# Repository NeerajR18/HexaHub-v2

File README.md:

# HexaHub-v2

NOTE: This is still a WIP project. Follow at your own risk!

A USB 2.0 Hub using the SL2.1A which has 4 downstream USB-A port and USB-C upstream port, with ESD and overcurrent protection enclosed in a 3D printed case with a hexagon-shaped PCB.

This USB Hub was made because of unavailability of the SL2.1S IC, which was used in the previous version and also as an improved version with polyfuses and ESD protection diodes.

This Hub was designed using KiCad and Autodesk Fusion for PCB and CAD Design. Fusion was also used for the case renders.

Made for Hack Club Fallout.

# PCB

- Schematic

- PCB without Ground Plane

- Overall PCB

# CAD

- Full Assembly

- Exploded View

# Renders
- Enclosed

- Exploded

# Build Guide
- Acquire your parts from your favourite platform.
- Order the PCB from your manufacturer
- Solder the components to the PCB
- 3D print the case, place PCB in the bottom, then close the top.
- Done!
If any footprints or 3D models are missing, you may use the footprints, symbols etc. from the Assets folder. Check your project folder and paths before importing.

# Bill of Materials

| MPN | Designator | Package | Quantity | Unit Price | Price (Ext.) | LCSC Link |
|---|---|---|---|---|---|---|
| SL2.1A | U1 | SOP-16 | 5 | 0.2677 | 1.34 | https://www.lcsc.com/product-detail/C6798314.html |
| 10.0 QHHTZB6.3 | J1 | SMD | 10 | 0.0665 | 0.67 | https://www.lcsc.com/product-detail/C668591.html |
| 676430910 | J2, J3, J4, J5 | Through Hole, Right Angle | 4 | 0.9415 | 3.77 | https://www.lcsc.com/product-detail/C2798029.html |
| 1206L200/24NR | F1 | 1206 | 5 | 0.1404 | 0.70 | https://www.lcsc.com/product-detail/C42396578.html |
| 1206L005/110WR | F2, F3, F4, F5 | 1206 | 5 | 0.1387 | 0.69 | https://www.lcsc.com/product-detail/C46422913.html |
| PRTR5V0U2X-ES | D1, D2, D3, D4, D5 | SOT-143 | 5 | 0.0404 | 0.20 | https://www.lcsc.com/product-detail/C5180302.html |
| X32258MOB4SI | Y1 | SMD3225-4P | 5 | 0.1738 | 0.87 | https://www.lcsc.com/product-detail/C2682775.html |
| RC0603FR-075K1L | R1, R2 | 0603 | 100 | 0.0018 | 0.18 | https://www.lcsc.com/product-detail/C105580.html |
| CL10A106KP8NNNC | C1, C2, C3, C4, C5, C6 | 0603 | 20 | 0.0108 | 0.22 | https://www.lcsc.com/product-detail/C19702.html |
| CC0402JRNPO9BN220 | C7, C8 | 0402 | 100 | 0.0012 | 0.12 | https://www.lcsc.com/product-detail/C106203.html |
| JLCPCB(PCB+shipping) | - | - | 5 | 4.66 | 14 | jlcpcb.com
| Total | - | - | - | 22.76 | - |
Apart from the IC, you may choose any brand of parts but with same package.

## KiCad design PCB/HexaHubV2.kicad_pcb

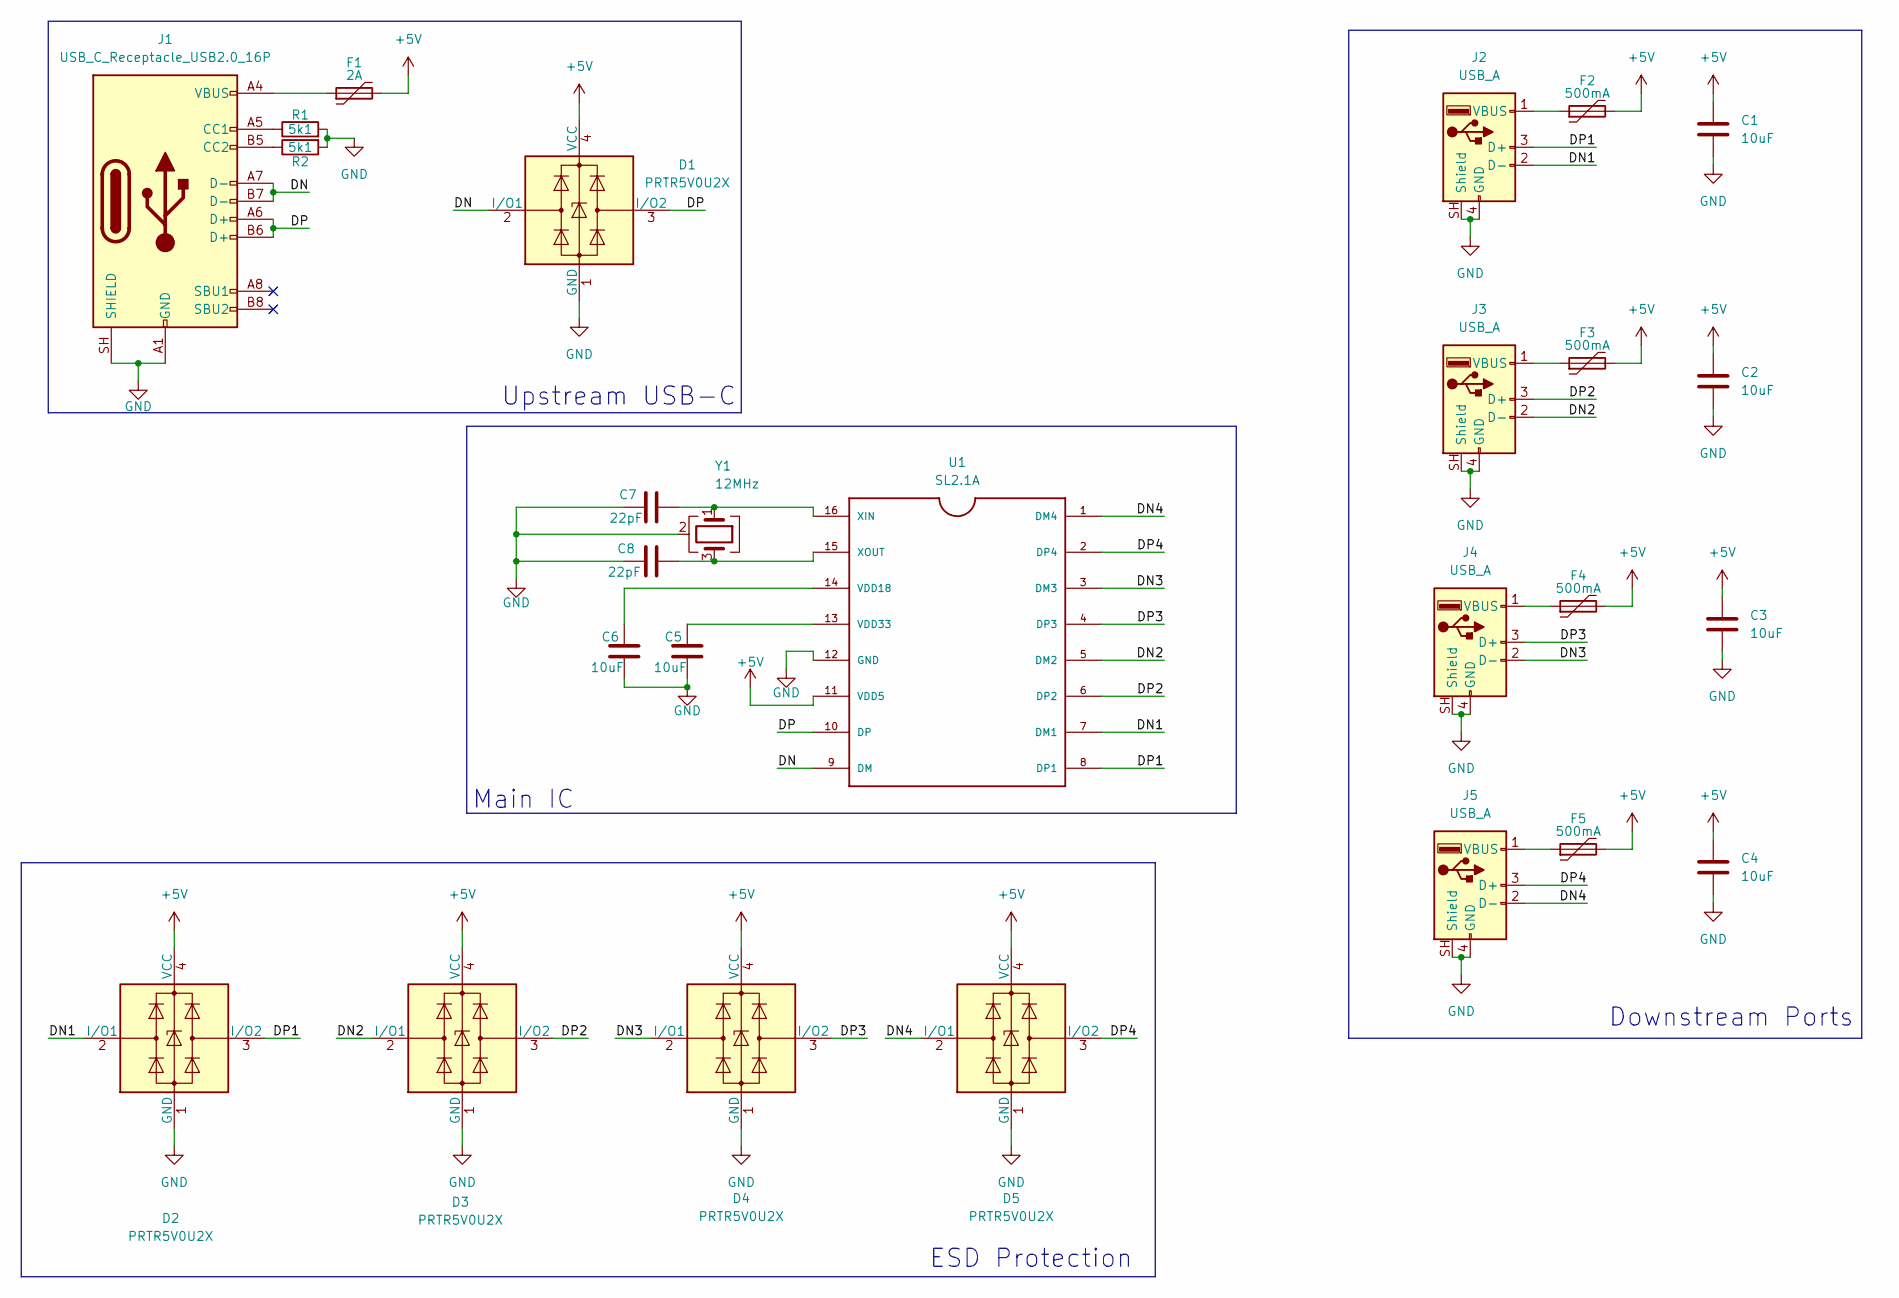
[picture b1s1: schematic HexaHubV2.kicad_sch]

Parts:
C1, C2, C3, C4, C5, C6: 10uF; C_0603_1608Metric
C7, C8: 22pF; C_0402_1005Metric
D1, D2, D3, D4, D5: PRTR5V0U2X; SOT-143
F1: 2A; Fuse_1206_3216Metric
F2, F3, F4, F5: 500mA; Fuse_1206_3216Metric
J1: USB_C_Receptacle_USB2.0_16P; USB_C_Receptacle_HRO_TYPE-C-31-M-12
J2, J3, J4, J5: USB_A; USB_A_Molex_67643_Horizontal
R1, R2: 5k1; R_0603_1608Metric
U1: SL2.1A; SO16
Y1: 12MHz; Crystal_SMD_3225-4Pin_3.2x2.5mm

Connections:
+5V: C1.1, C2.1, C3.1, C4.1, D1.4 (VCC), D2.4 (VCC), D3.4 (VCC), D4.4 (VCC), D5.4 (VCC), F1.2, F2.2, F3.2, F4.2, F5.2, U1.11 (VDD5)
/DN: D1.2 (I/O1), J1.A7 (D-), J1.B7 (D-), U1.9 (DM)
/DN1: D2.2 (I/O1), J2.2 (D-), U1.7 (DM1)
/DN2: D3.2 (I/O1), J3.2 (D-), U1.5 (DM2)
/DN3: D4.2 (I/O1), J4.2 (D-), U1.3 (DM3)
/DN4: D5.2 (I/O1), J5.2 (D-), U1.1 (DM4)
/DP: D1.3 (I/O2), J1.A6 (D+), J1.B6 (D+), U1.10 (DP)
/DP1: D2.3 (I/O2), J2.3 (D+), U1.8 (DP1)
/DP2: D3.3 (I/O2), J3.3 (D+), U1.6 (DP2)
/DP3: D4.3 (I/O2), J4.3 (D+), U1.4 (DP3)
/DP4: D5.3 (I/O2), J5.3 (D+), U1.2 (DP4)
GND: C1.2, C2.2, C3.2, C4.2, C5.1, C6.1, C7.2, C8.2, D1.1 (GND), D2.1 (GND), D3.1 (GND), D4.1 (GND), D5.1 (GND), J1.A1 (GND), J1.A12 (GND), J1.B1 (GND), J1.B12 (GND), J1.SH (SHIELD), J2.4 (GND), J2.SH (Shield), J3.4 (GND), J3.SH (Shield), J4.4 (GND), J4.SH (Shield), J5.4 (GND), J5.SH (Shield), R1.2, R2.2, U1.12 (GND), Y1.2 (G), Y1.4 (G)
unnamed: F1.1, J1.A4 (VBUS), J1.A9 (VBUS), J1.B4 (VBUS), J1.B9 (VBUS)
unnamed: J1.A5 (CC1), R1.1
unnamed: J1.B5 (CC2), R2.1
unnamed: F2.1, J2.1 (VBUS)
unnamed: F3.1, J3.1 (VBUS)
unnamed: F4.1, J4.1 (VBUS)
unnamed: F5.1, J5.1 (VBUS)
unnamed: C6.2, U1.14 (VDD18)
unnamed: C5.2, U1.13 (VDD33)
unnamed: C7.1, U1.16 (XIN), Y1.1
unnamed: C8.1, U1.15 (XOUT), Y1.3

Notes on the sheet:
ESD Protection
Main IC
Downstream Ports
Upstream USB-C

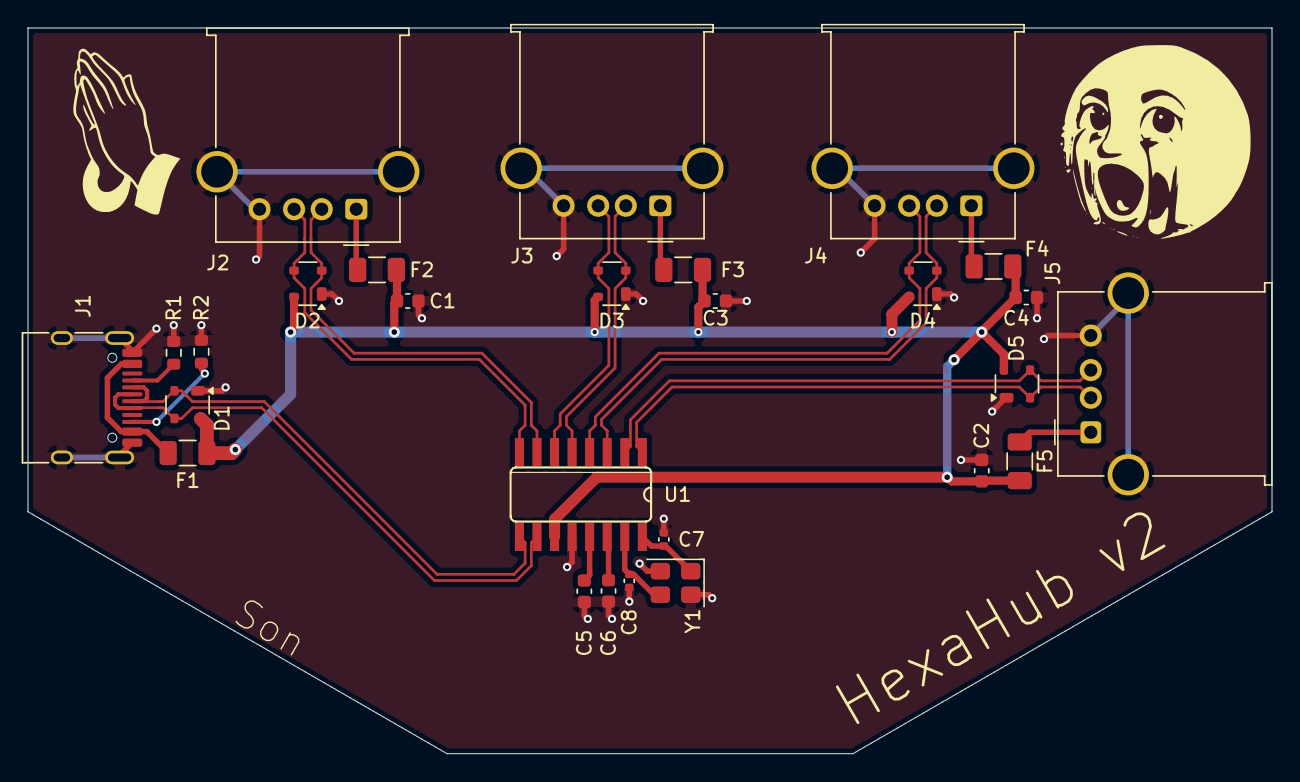
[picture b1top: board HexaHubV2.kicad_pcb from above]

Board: 2 copper layers, 90.0 x 52.5 mm, 27 parts (0 on the bottom side), 23 nets.

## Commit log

2026-05-24 Added PCB files and gerbers
2026-05-24 Slight changes to PCB and updated gerbers
2026-05-24 Added BOM, footprints and 3d models
    BOM and footprint, symbol and 3d model of SL2.1A and Type-C port
2026-05-24 Added Type-C 3D model
2026-05-24 Added CAD files
2026-05-24 Updated README
    Added project details, build guide, and bill of materials to README.
2026-05-25 Slight changes to PCB
2026-05-25 Added zine page and renders, updated PCB images
2026-05-25 Added zine.pdf to main
2026-06-01 updated CAD files
